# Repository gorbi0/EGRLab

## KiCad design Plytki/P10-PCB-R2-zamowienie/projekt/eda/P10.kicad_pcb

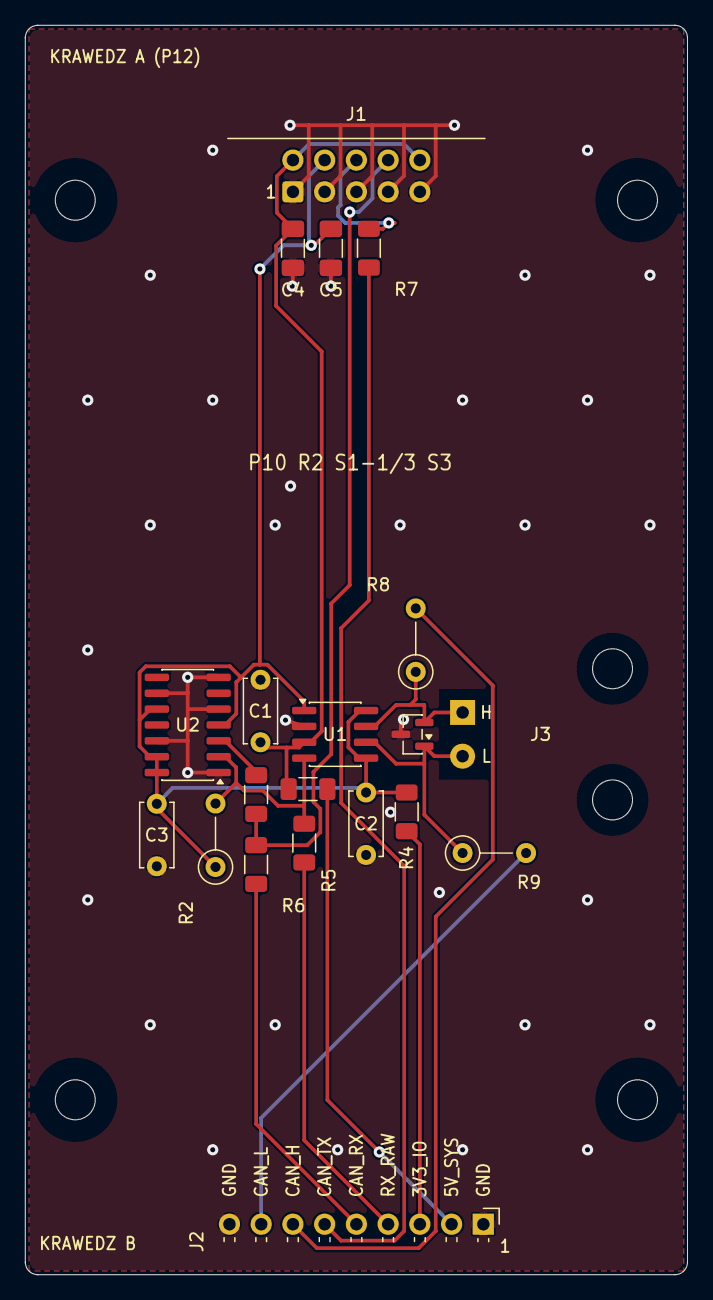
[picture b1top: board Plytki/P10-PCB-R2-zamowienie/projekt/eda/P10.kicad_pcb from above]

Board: 2 copper layers, 53.0 x 100.0 mm, 24 parts (0 on the bottom side), 16 nets.

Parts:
C1, C2, C3: 100n; C_Disc_D5.0mm_W2.5mm_P5.00mm
C4, C5: 4u7; C_1206_3216Metric_Pad1.33x1.80mm_HandSolder
D1: PESD2CAN; SOT-23
H1, H2, H3, H4: M3 NPTH
J1: J_BP; IDC-Header_2x05_P2.54mm_Horizontal
J2: SERWIS; PinHeader_1x09_P2.54mm_Horizontal
J3: OBD; PTH_OBD
R1: 100R; R_1206_3216Metric_Pad1.30x1.75mm_HandSolder
R2, R8, R9: 10K; R_Axial_DIN0207_L6.3mm_D2.5mm_P5.08mm_Vertical
R3, R4, R5, R6, R7: 1K; R_1206_3216Metric_Pad1.30x1.75mm_HandSolder
U1: TCAN1051V; SOIC-8_3.9x4.9mm_P1.27mm
U2: 74LVC125AD; SOIC-14_3.9x8.7mm_P1.27mm

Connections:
3V3_IO: C2.1, C3.1, C5.1, J1.4, R2.1, R4.1, U1.1, U1.5, U1.8, U2.4, U2.10, U2.13, U2.14
5V_SYS: C1.1, C4.1, J1.2, J1.10, R3.1, U1.3
/CORE/CAN_RX: J1.8, R1.2, R6.1
/CORE/CAN_TX: J1.6, R7.1
/CORE/RX_BUF: R1.1, U2.3
/CORE/SRV_3V3_IO: J2.3, R4.2
/CORE/SRV_5V_SYS: J2.2, R3.2
/CORE/SRV_CAN_H: J2.7, R8.2
/CORE/SRV_CAN_L: J2.8, R9.2
/CORE/SRV_CAN_RX: J2.5, R6.2
/CORE/SRV_CAN_TX: J2.6, R7.2
/CORE/SRV_RX_RAW: J2.4, R5.2
CAN_H: D1.2, J3.1, R8.1, U1.7
CAN_L: D1.1, J3.2, R9.1, U1.6
GND: C1.2, C2.2, C3.2, C4.2, C5.2, D1.3, J1.1, J1.3, J1.5, J1.7, J1.9, J2.1, J2.9, U1.2, U2.1, U2.5, U2.7, U2.9, U2.12
RX_RAW: R2.2, R5.1, U1.4, U2.2

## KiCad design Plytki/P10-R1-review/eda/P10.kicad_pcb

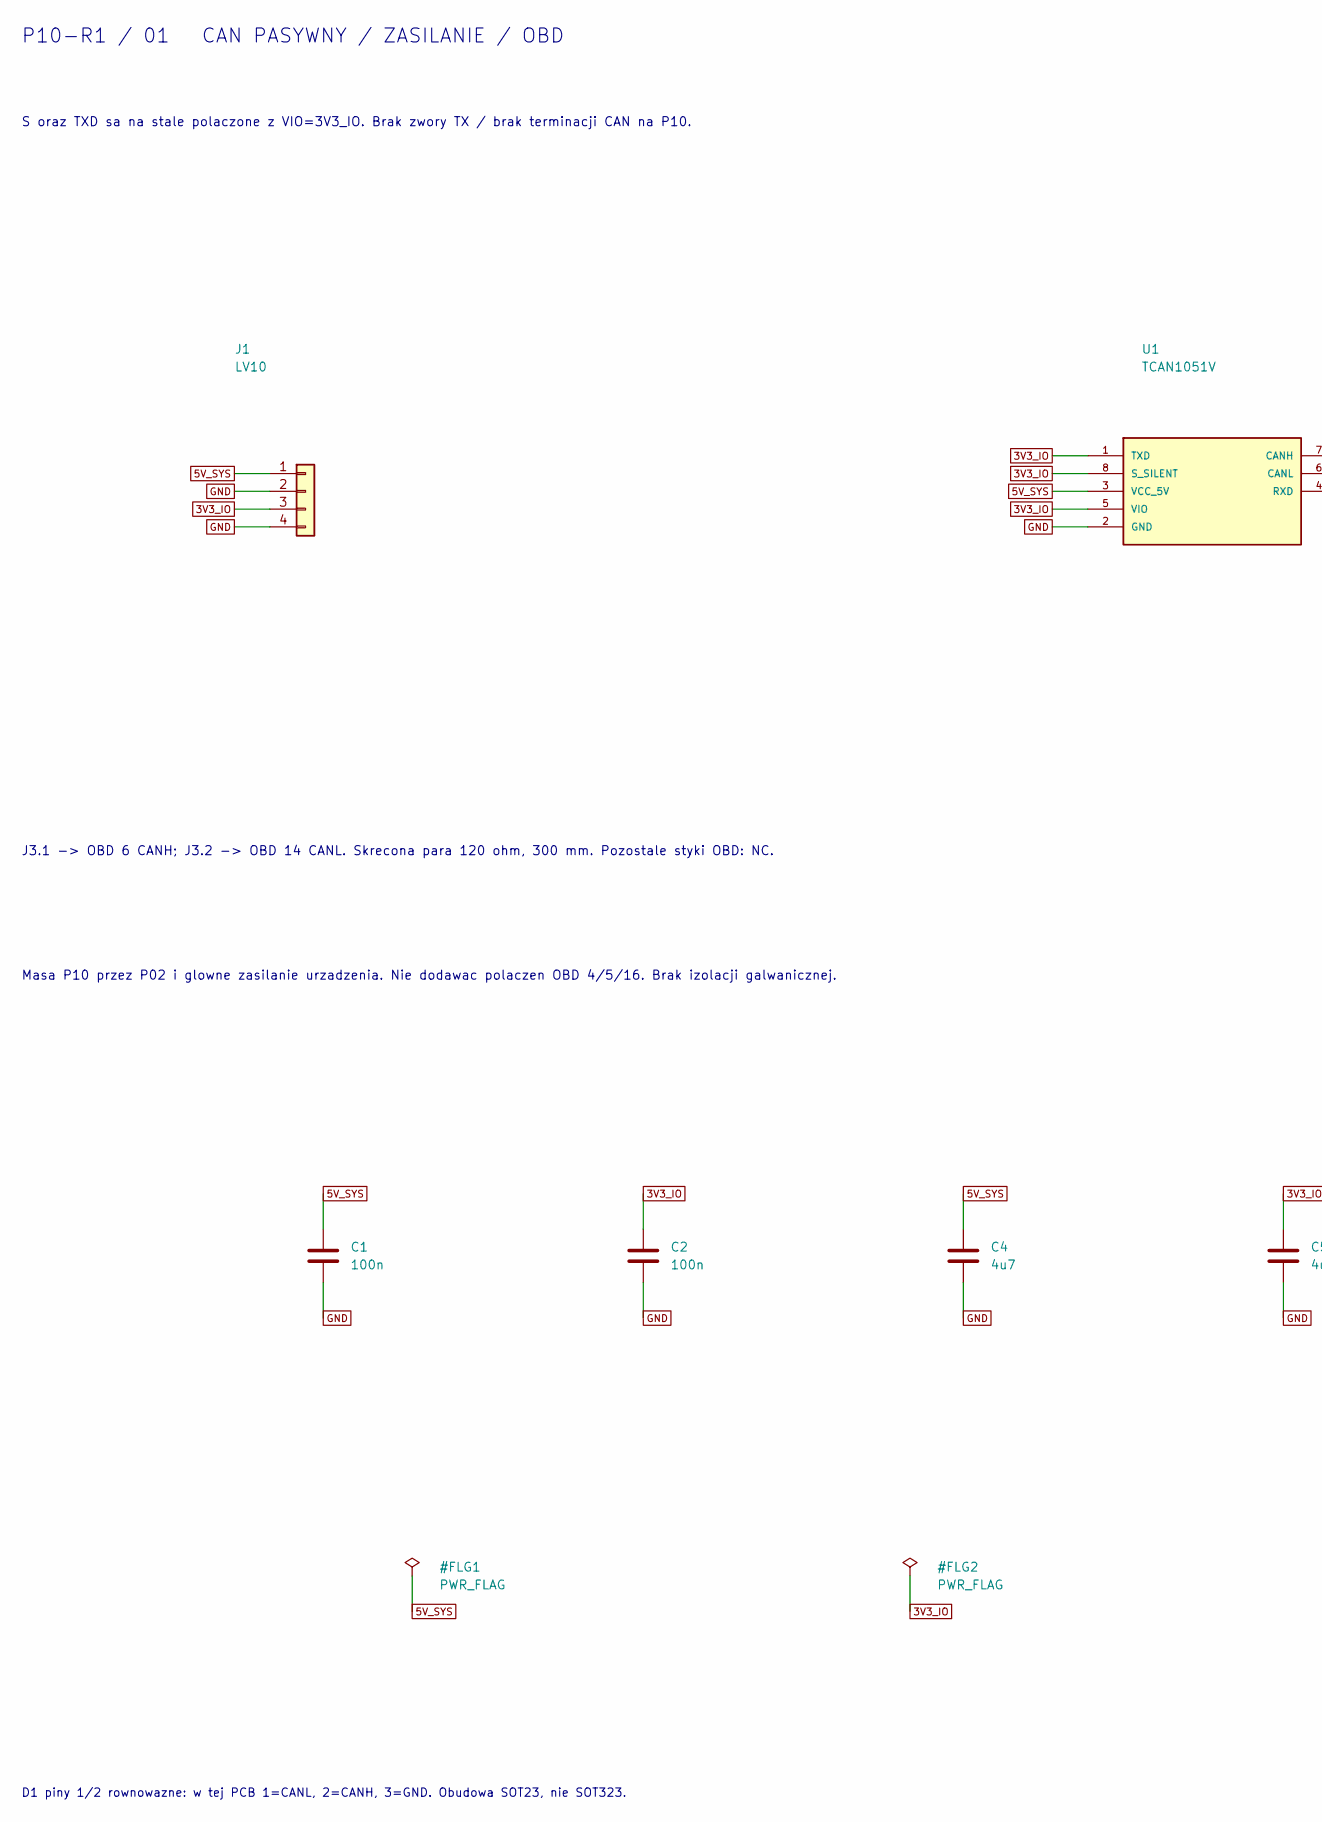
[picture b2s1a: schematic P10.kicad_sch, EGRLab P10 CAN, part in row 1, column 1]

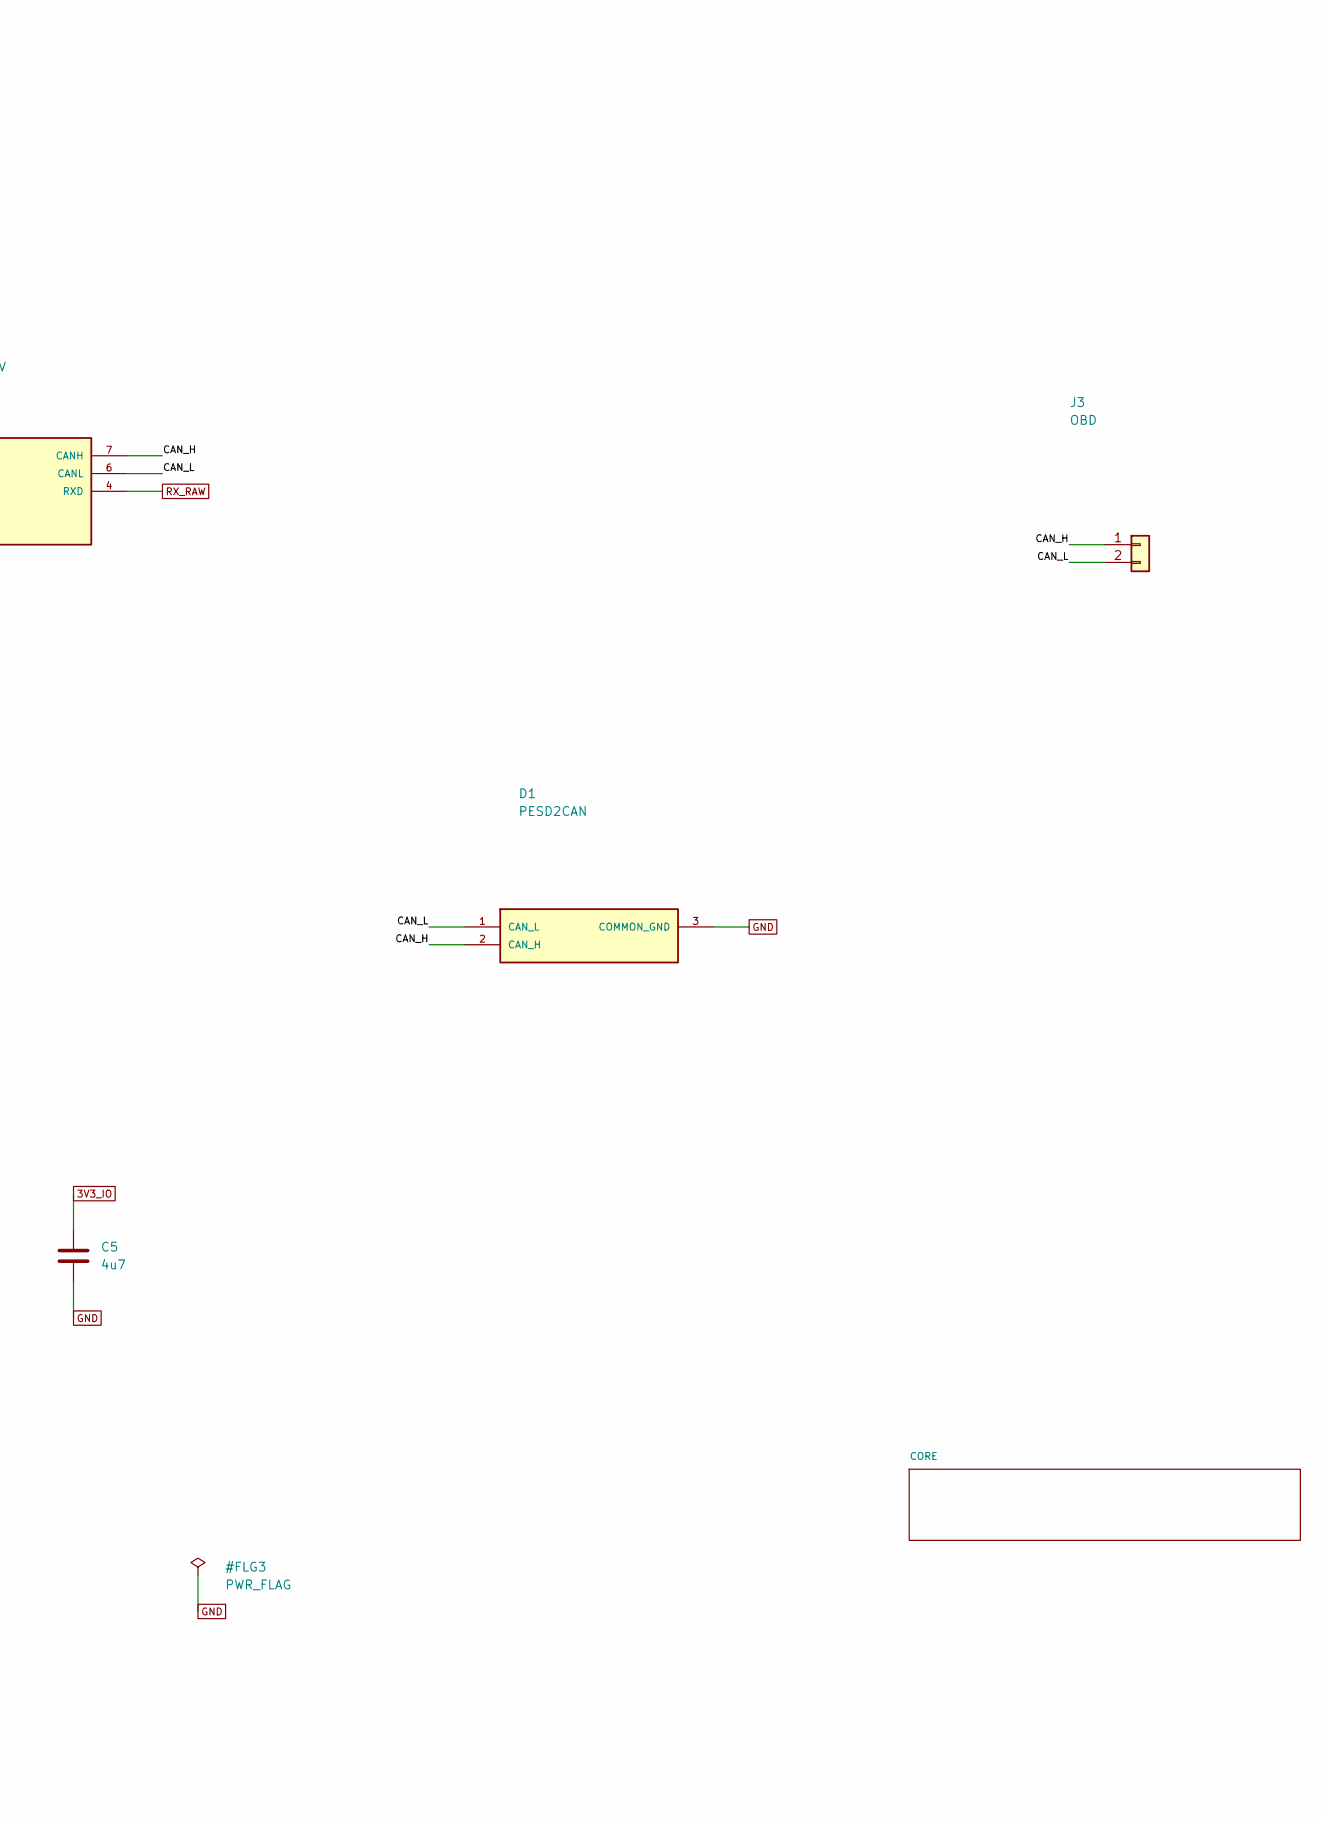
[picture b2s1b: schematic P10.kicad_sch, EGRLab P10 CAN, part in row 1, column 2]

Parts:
C1, C2: 100n; C_0805_2012Metric; MPN X7R 25V 10% 0805 100n
C4, C5: 4u7; C_0805_2012Metric; MPN X7R 25V 10% 0805 4u7
D1: PESD2CAN; SOT-23; MPN PESD2CAN,215 Nexperia
J1: LV10; PTH_LV10; MPN Soldered harness
J3: OBD; PTH_OBD; MPN Soldered 120ohm twisted pair
U1: TCAN1051V; SOIC-8_3.9x4.9mm_P1.27mm; MPN TCAN1051VDRQ1

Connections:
3V3_IO: C2.1, C5.1, J1.3, U1.1 (TXD), U1.5 (VIO), U1.8 (S_SILENT); also elsewhere on the board
5V_SYS: C1.1, C4.1, J1.1, U1.3 (VCC_5V); also elsewhere on the board
/CAN_H: D1.2 (CAN_H), J3.1, U1.7 (CANH)
/CAN_L: D1.1 (CAN_L), J3.2, U1.6 (CANL)
GND: C1.2, C2.2, C4.2, C5.2, D1.3 (COMMON_GND), J1.2, J1.4, U1.2 (GND); also elsewhere on the board
RX_RAW: U1.4 (RXD); also elsewhere on the board

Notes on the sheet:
S oraz TXD sa na stale polaczone z VIO=3V3_IO. Brak zwory TX / brak terminacji CAN na P10.
J3.1 -> OBD 6 CANH; J3.2 -> OBD 14 CANL. Skrecona para 120 ohm, 300 mm. Pozostale styki OBD: NC.
Masa P10 przez P02 i glowne zasilanie urzadzenia. Nie dodawac polaczen OBD 4/5/16. Brak izolacji galwanicznej.
D1 piny 1/2 rownowazne: w tej PCB 1=CANL, 2=CANH, 3=GND. Obudowa SOT23, nie SOT323.
P10-R1 / 01 CAN PASYWNY / ZASILANIE / OBD

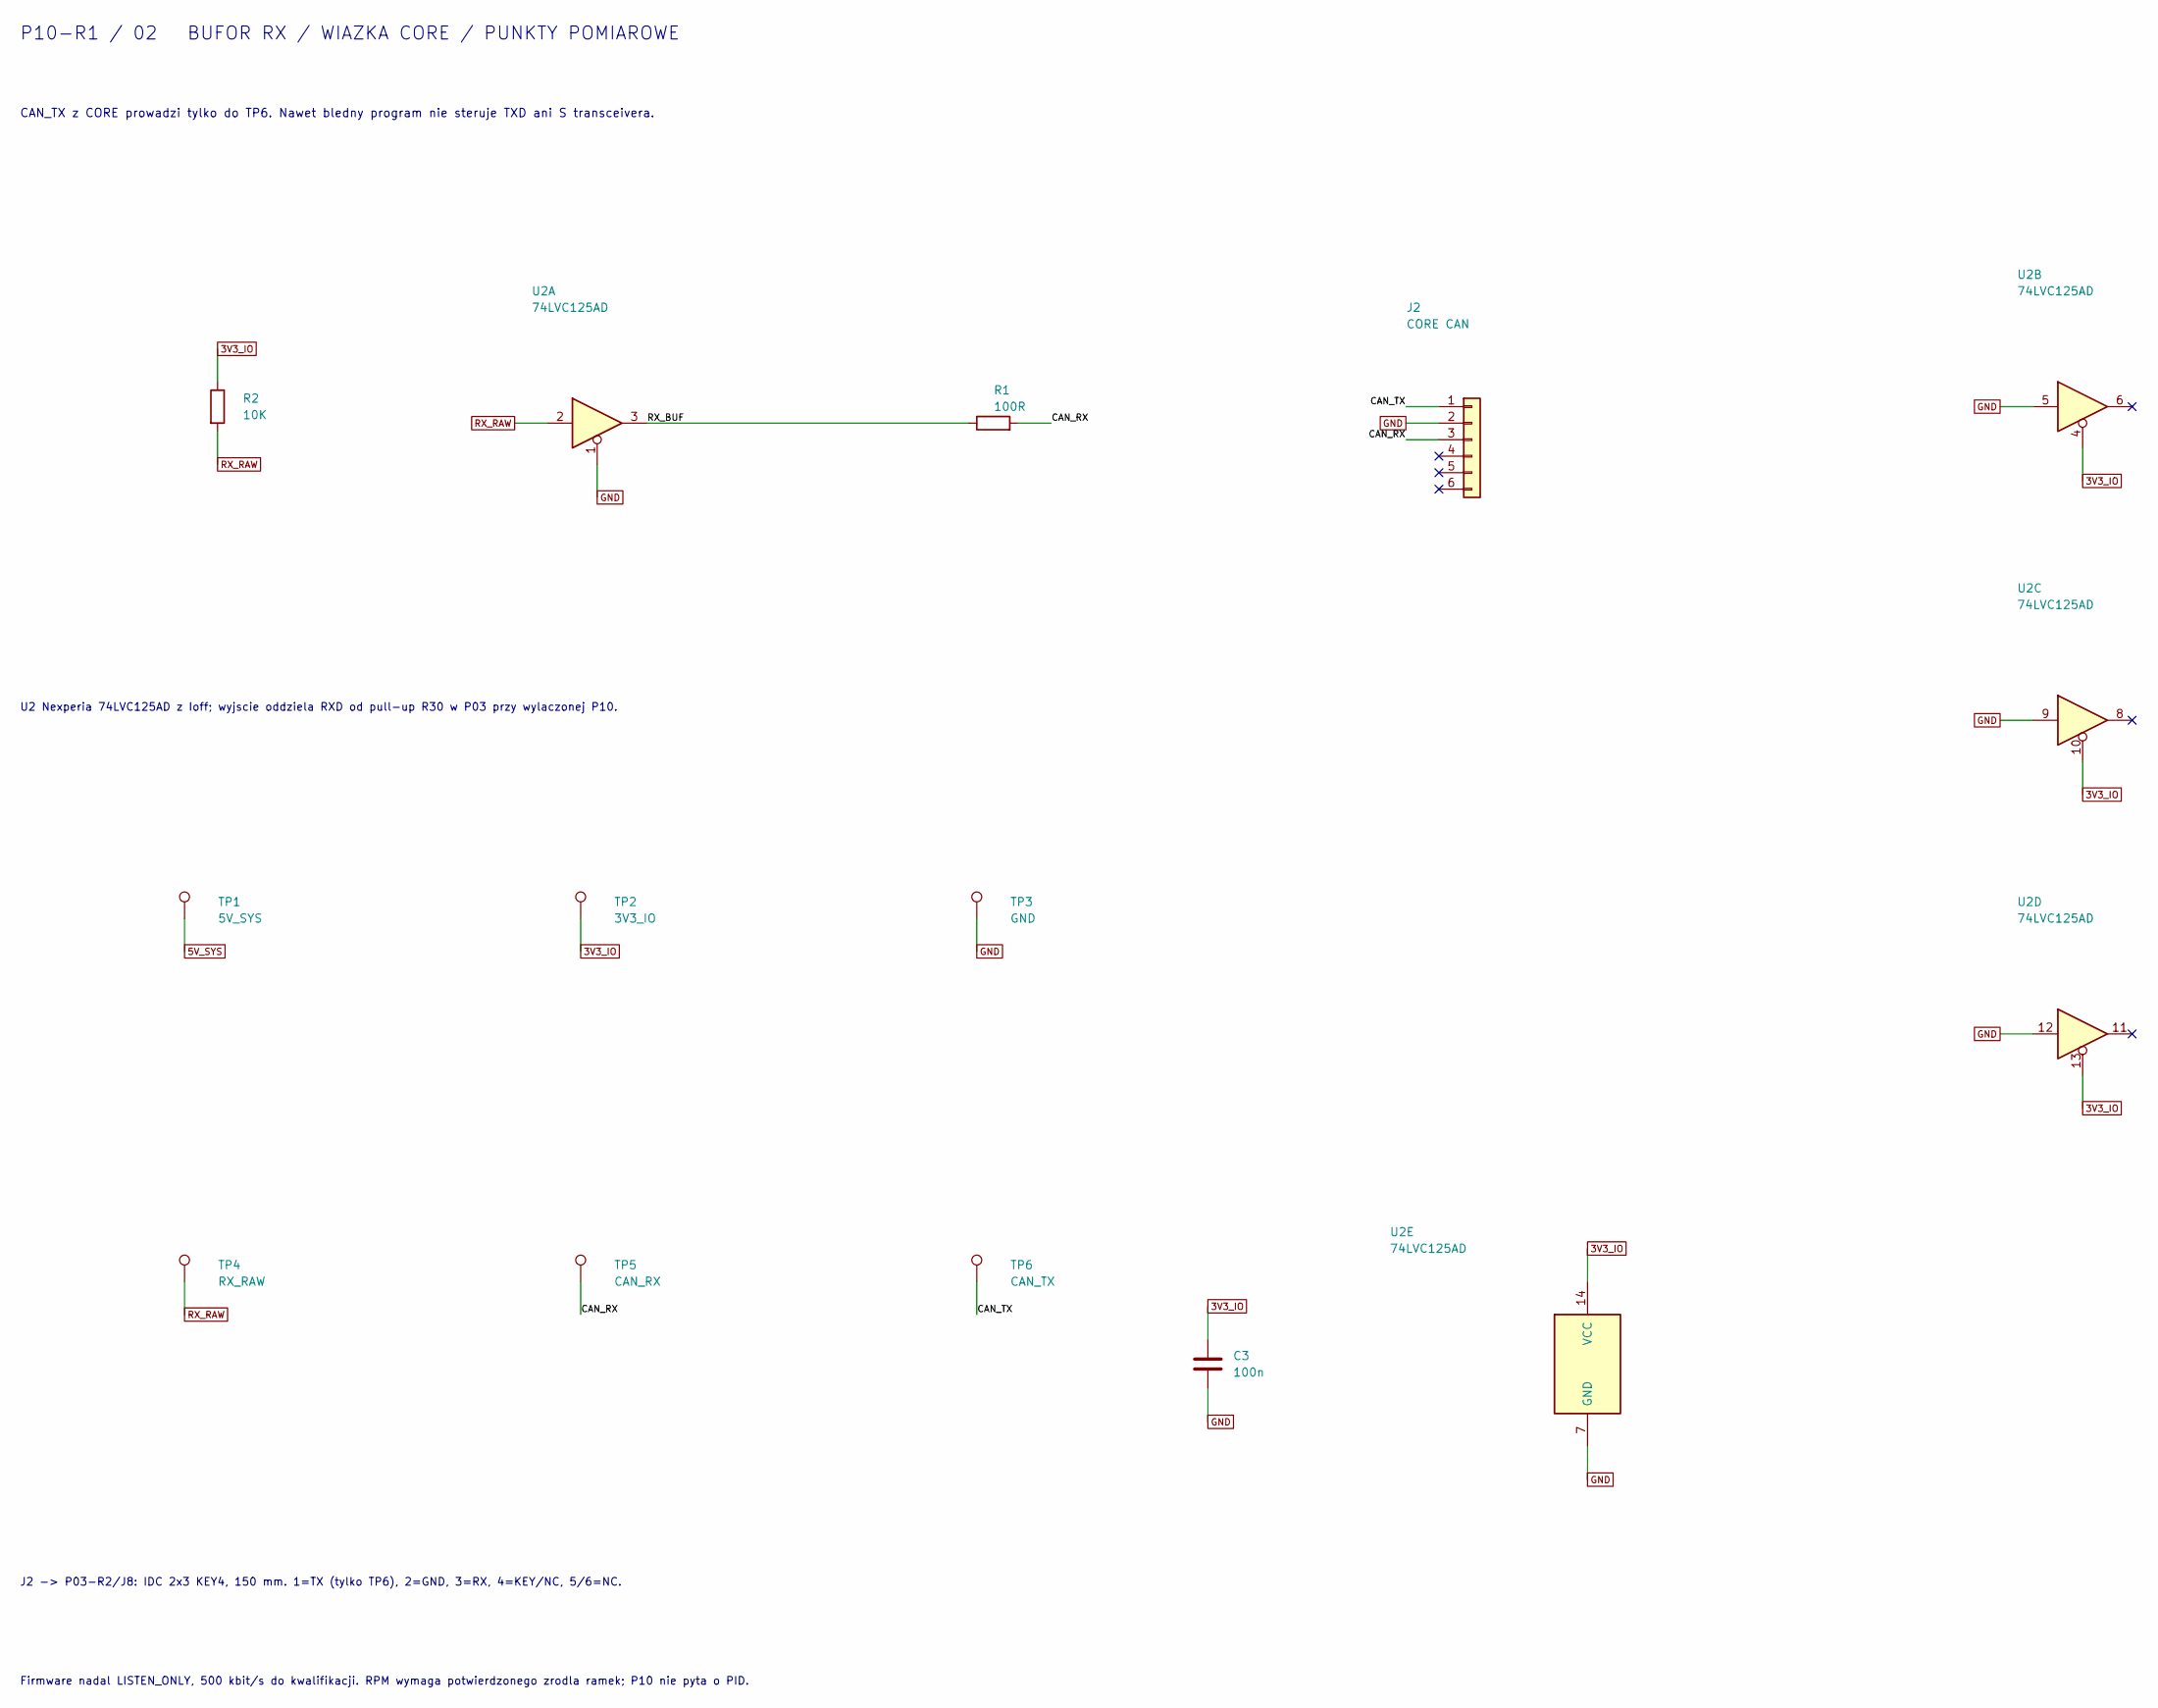
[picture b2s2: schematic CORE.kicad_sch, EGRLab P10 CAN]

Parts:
C3: 100n; C_0805_2012Metric; MPN X7R 25V 10% 0805 100n
J2: CORE CAN; PTH_CAN_CORE; MPN Soldered ribbon 6p
R1: 100R; R_Axial_DIN0207_L6.3mm_D2.5mm_P10.16mm_Horizontal; MPN Metal film 100R 1% 0.25W
R2: 10K; R_Axial_DIN0207_L6.3mm_D2.5mm_P10.16mm_Horizontal; MPN Metal film 10K 1% 0.25W
TP1: 5V_SYS; TestPad_1; MPN PCB test pad
TP2: 3V3_IO; TestPad_1; MPN PCB test pad
TP3: GND; TestPad_1; MPN PCB test pad
TP4: RX_RAW; TestPad_1; MPN PCB test pad
TP5: CAN_RX; TestPad_1; MPN PCB test pad
TP6: CAN_TX; TestPad_1; MPN PCB test pad
U2: 74LVC125AD; SOIC-14_3.9x8.7mm_P1.27mm; MPN 74LVC125AD,118 Nexperia

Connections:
3V3_IO: C3.1, R2.1, TP2.1, U2.4, U2.10, U2.13, U2.14 (VCC); also elsewhere on the board
5V_SYS: TP1.1; also elsewhere on the board
/CORE/CAN_RX: J2.3, R1.2, TP5.1
/CORE/CAN_TX: J2.1, TP6.1
/CORE/RX_BUF: R1.1, U2.3
GND: C3.2, J2.2, TP3.1, U2.1, U2.5, U2.7 (GND), U2.9, U2.12; also elsewhere on the board
RX_RAW: R2.2, TP4.1, U2.2; also elsewhere on the board

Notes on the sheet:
CAN_TX z CORE prowadzi tylko do TP6. Nawet bledny program nie steruje TXD ani S transceivera.
U2 Nexperia 74LVC125AD z Ioff; wyjscie oddziela RXD od pull-up R30 w P03 przy wylaczonej P10.
J2 -> P03-R2/J8: IDC 2x3 KEY4, 150 mm. 1=TX (tylko TP6), 2=GND, 3=RX, 4=KEY/NC, 5/6=NC.
Firmware nadal LISTEN_ONLY, 500 kbit/s do kwalifikacji. RPM wymaga potwierdzonego zrodla ramek; P10 nie pyta o PID.
P10-R1 / 02 BUFOR RX / WIAZKA CORE / PUNKTY POMIAROWE

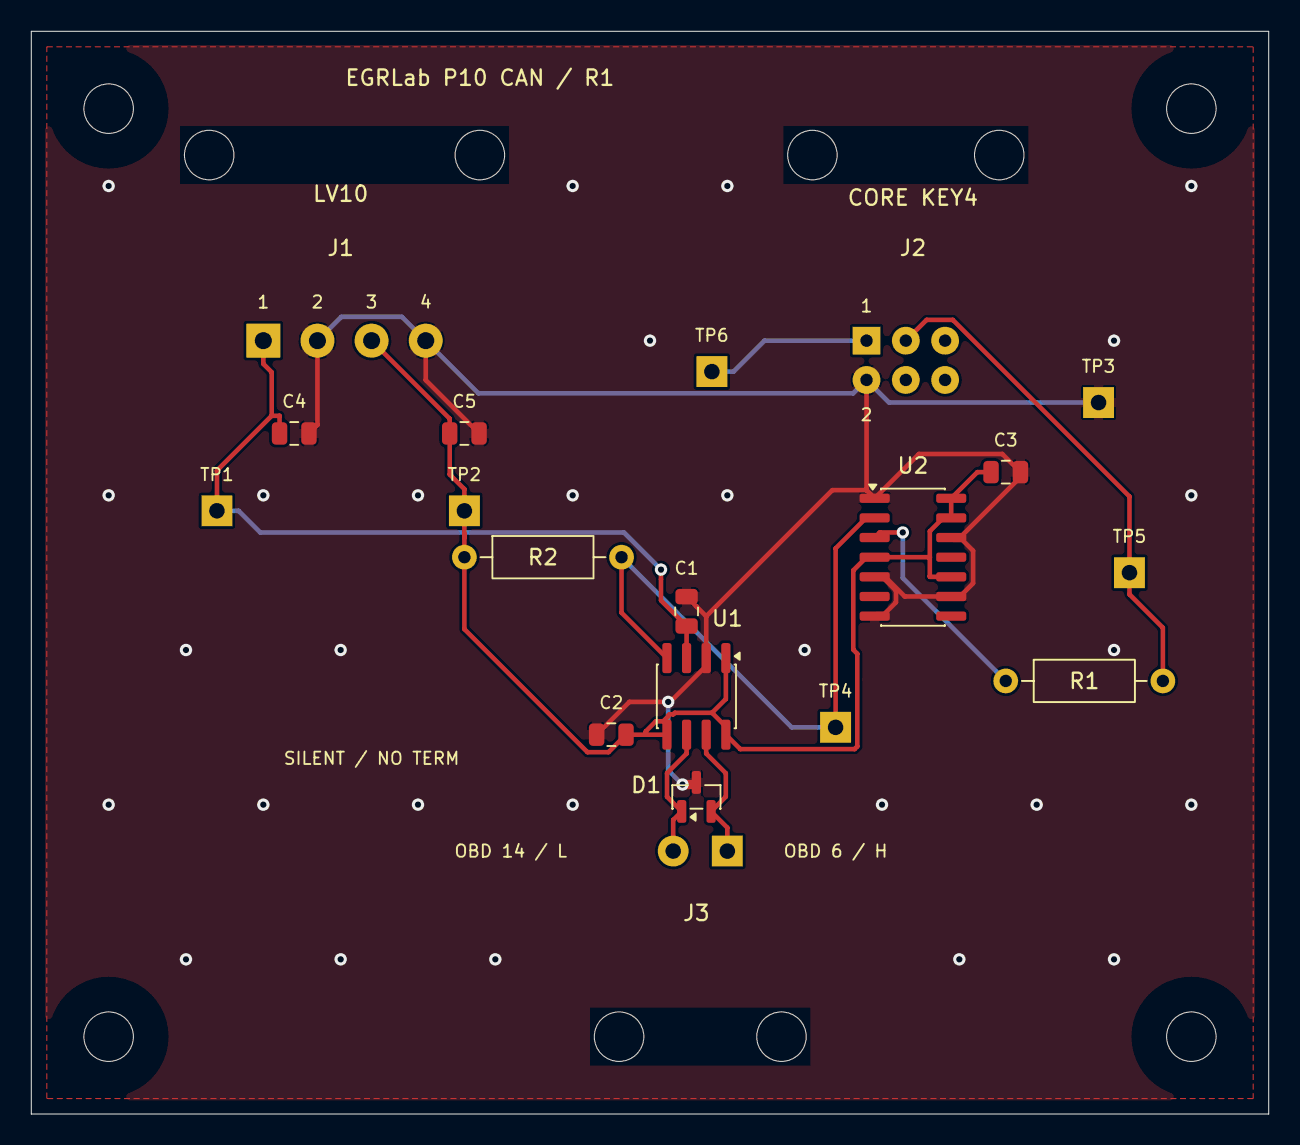
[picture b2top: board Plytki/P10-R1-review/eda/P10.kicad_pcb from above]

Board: 2 copper layers, 80.0 x 70.0 mm, 23 parts (0 on the bottom side), 9 nets.

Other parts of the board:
H1, H2, H3, H4: M3 NPTH
